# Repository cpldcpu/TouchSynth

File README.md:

# TouchSynth

**[Blog article](https://cpldcpu.github.io/2026/11/14/touchsynth/)** · **[Audio samples](https://cpldcpu.github.io/TouchSynth/)**

---

A small MCU-controlled analog monophonic synthesizer on a 100 × 100 mm, 4-layer PCB. It has no
potentiometers and no mechanical switches: 13 capacitive touch keys plus SHIFT / − / + play and edit it, and
16 LEDs show the settings. A CH32V003 (or CH32V002 / V006) generates the oscillator timing and four
PWM control voltages for a discrete analog voice:

- **DCO:** a TL072 integrator reset by the MCU timer. The charge current tracks pitch, so the saw amplitude
  stays flat. Saw, variable-width pulse, sub-oscillator and noise.
- **VCF:** a 24 dB/oct transistor ladder (BC847BS) with an expo converter and resonance up to self-oscillation.
- **VCA:** a differential-pair VCA. An 8-bit R-2R trim DAC nulls the CV feedthrough ("thump").
- **Line out,** an audio loopback into the MCU ADC (for calibration and tests), and an optional MIDI in.

All assembled parts are JLCPCB **Basic** or **Promotional Extended** parts: 40 BOM lines, 196 placements,
about USD 3.65 of parts per board at list price. The MCU, headers and MIDI parts are hand-soldered.

**Status (2026-10-18):** board 1 (rev 0.1, CH32V006) is built and brought up. It passes the bring-up steps
and functional tests T1, T2 and T4–T12 (noise marginal at about −55 dB); T3 (touch scan rate) and T14 (MIDI)
have not been measured. The results are in the
[design report](docs/report/touchsynth_report.pdf), section 10. Firmware 0.1 runs on the board, including
multitrack demo pieces and percussion presets. Calibration storage in flash is still open.

The `polyphonic_exp` branch experiments with extensions. So far it turns the pulse output into a PWM DAC
(CH32V006) for digital voices through the analog filter and VCA, starting with a modal timpani, the *kettle*
([kettle_model.mp3](docs/audio/pieces/kettle_model.mp3); report, section 10.5).

Design: cpldcpu & Claude Opus 5.5.

## Hear it

Recorded from board 1's line out. The synth is monophonic, so the multitrack pieces were played one part at a
time and mixed:

| Piece | Board 1 | Model |
|---|---|---|
| *TouchSynth Demo*, original, 7 parts (drums, acid bass, arp, lead, pad) | [demo_hw](docs/audio/demo/touchsynth_demo_hw.mp3) | [demo_model](docs/audio/demo/touchsynth_demo_model.mp3) |
| Purcell, *Queen Mary's March*: 4 trumpets, bass, timpani (modal synthesis on the PWM DAC) | [march_hw](docs/audio/pieces/march_hw.mp3) | [march_model](docs/audio/pieces/march_model.mp3) |
| Bach, Toccata BWV 565, mm. 1–30: 9 organ voices | [toccata_hw](docs/audio/pieces/toccata_hw.mp3) | [toccata_model](docs/audio/pieces/toccata_model.mp3) |
| *Aerosphere*, original space-synth piece, 8 parts | [aero_hw](docs/audio/pieces/aero_hw.mp3) | [aero_model](docs/audio/pieces/aero_model.mp3) |
| Suite: Aerosphere intro into the Toccata | [suite_hw](docs/audio/pieces/suite_hw.mp3) | [suite_model](docs/audio/pieces/suite_model.mp3) |

The three built-in demo tunes (SHIFT + C' on the board), recorded from board 1:
[acid](docs/audio/hw_board1/tune_acid.mp3), [prelude](docs/audio/hw_board1/tune_prelude.mp3) (Bach BWV 846) and
[ode](docs/audio/hw_board1/tune_ode.mp3) (Beethoven). Also from the board: a
[waveform tour](docs/audio/hw_board1/waveforms.mp3) and a [scale on the self-oscillating filter](docs/audio/hw_board1/selfosc_scale.mp3).
The behavioural model renders every single feature (waveforms, filter, envelopes, glide, …) in
[docs/audio/features/](docs/audio/features/). [docs/README.md](docs/README.md) lists all audio files.

## Documents

| Document | Content |
|---|---|
| [docs/report/touchsynth_report.pdf](docs/report/touchsynth_report.pdf) | **design report**: requirements, architecture, circuits, simulations, PCB, BOM, firmware, demo tunes and instruments, V&V with the board 1 results |
| [docs/README.md](docs/README.md) | index of everything in `docs/`: documents, figures, result data, audio |
| [docs/spec.md](docs/spec.md) | specification and design decisions (some pre-layout details are outdated; the report is current) |
| [docs/sim_report.md](docs/sim_report.md) | simulation report S1–S7 and the behavioural model |
| [docs/verification_plan.md](docs/verification_plan.md) | bring-up, functional tests, calibration and validation, board 1 results |
| [docs/touchsynth_schematic.pdf](docs/touchsynth_schematic.pdf) | schematic (7 sheets) |
| [firmware/touchsynth/README.md](firmware/touchsynth/README.md) | firmware build, playing instructions and test console |
| [hw/README.md](hw/README.md) | schematic generator scripts |

## Repository layout

```
docs/        report (LaTeX), spec, simulation report, V&V plan, figures, audio examples, result CSVs
sim/         ngspice simulations S1–S7 (one folder per block), shared netlists and models, behavioural model
hw/          design.py (single source of truth) -> KiCad schematic, PCB, routing and fab outputs
  touchsynth/  KiCad 10 project (generated; edit the Python sources, not the KiCad files)
firmware/    touchsynth/ firmware 0.1, ch32fun (git submodule)
parts/       JLCPCB Basic / Promotional Extended part lists
tools/       bench tools: hardware tests, scope recording, multitrack mixing, figures; Freerouting jar (not in git)
```

## Flow

Every stage is generated by scripts from [hw/design.py](hw/design.py), which holds the parts, values, LCSC
numbers and nets.

```
simulate      sim/s*/s*.py                 ngspice-42 in WSL -> docs/results/*.csv, docs/figures/*.png
model         sim/behav/validate.py        behavioural model vs. ngspice
              sim/behav/examples.py        audio examples + spectrograms
schematic     hw/gen_sch2.py               -> hw/touchsynth/*.kicad_sch
              hw/check_netlist.py          KiCad netlist == design.py
              hw/check_sim.py              design.py == simulation netlists
PCB           hw/gen_pcb.py [--route]      placement, silkscreen art, planes, Freerouting + GND stitching
              hw/gen_pcb.py --finish       post-route clean-up (islands, leftovers via the A* router)
fab           hw/fab.py                    gerbers, drill, BOM and CPL -> hw/touchsynth/production/
report        docs/report/gen_tables.py    then: latexmk -pdf touchsynth_report.tex (WSL)
firmware      firmware/touchsynth/gen_tables.py, check_pins.py, make
tunes         sim/behav/tunes.py, pieces.py    demo tunes, multitrack pieces and presets (-> firmware tables)
bench         tools/hwtest.py              functional tests over the SWIO console -> docs/results/hw_board1*
              tools/hw_figures.py          board 1 figures for the report
              tools/record_parts.sh        record one multitrack part per take with the scope (on the lab PC)
              tools/mix_parts.py, suite.py align, clock-correct and mix the takes -> docs/audio/
```

The bench tools need the lab setup (the PC with the programmer, the scope address) in `tools/lab.conf`: copy
[tools/lab.conf.example](tools/lab.conf.example) and edit it; `lab.conf` is not in git.

`gen_pcb.py` needs KiCad's bundled Python (`pcbnew`) and Java 17 for Freerouting 1.9.0. The hw scripts find KiCad 10
in its standard install folder, or in `KICAD_DIR` if set. The other Python
scripts use a normal Python 3 with numpy and matplotlib. ngspice, LaTeX and the RISC-V toolchain run in WSL.

## Key numbers

| | |
|---|---|
| Supply | 9–12 V DC, about 31 mA (simulated); board 1: 25 mA, MCU running, LEDs off |
| Pitch range | C1 … C8, saw amplitude flat within ±2.2 % |
| Filter | 20 Hz … 20 kHz cutoff, −23 dB/oct, self-oscillation |
| VCA | 121 dB off-attenuation, thump < 0.6 mV after trim |
| Output | about 1.2 Vpp line level, AC-coupled |
| Control | 4 × 12-bit CV (10-bit PWM at 46.9 kHz + 2-bit dither), 1 kHz envelope / LFO rate |
| Touch | 16 pads via 2 × CD4051, 1.4 kHz scan |
| PCB | 100 × 100 mm, 4 layers (signal / GND / split power / signal), 242 parts, 166 nets |

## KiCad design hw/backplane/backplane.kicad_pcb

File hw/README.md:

# Hardware generator scripts (KiCad 10)

Everything here is generated from Python; edit the sources, not the `.kicad_sch` files. The scripts serve several
boards; `BOARD` selects one (`board.py`):

| `BOARD` | Design | Output | Status |
|---|---|---|---|
| `voice` (default) | `voice.py`: the voice card (docs/spec.md section 3) | `voice/` | schematic generated, hand-laid out (`layouts_voice.py`) and checked; PCB generated and routed (`voice/voice.kicad_pcb`, 50 × 50 mm, 4 layers, DRC clean, stereo pan stage S13 A) |
| `backplane` | `backplane.py`: the backplane and controller (docs/backplane.md) | `backplane/` | schematic hand-laid out (`layouts_backplane.py`) and checked (mixer against S12 `--bus2`); PCB generated and routed (`gen_pcb_bp.py`, 100 × 100 mm, 4 layers: In1 GND, In2 +3V3 / GND; DRC clean); host port fitted, slot 1 convertible to an effects slot (backplane.md 5.1) |
| `touchsynth` | `design.py`: TouchSynth rev 0.1, for reference | `touchsynth/` (its KiCad project is on `master`) | |

| File | Role |
|---|---|
| `voice.py`, `design.py` | single source of truth per board: parts (value, footprint, LCSC, sim name), nets, sheets, groups; `voice.py` also maps its simulation netlist (S13 variant A on S10 v5c) to its nets |
| `board.py` | board selection (`BOARD`), project name, power nets, layout module |
| `lcsc.py` | picks JLCPCB basic / promotional parts for passives (voltage rating >= 2x working voltage; C0G on request) |
| `layouts_voice.py`, `layouts_backplane.py`, `layouts.py` | hand-drawn sheet layouts of the voice card, the backplane and rev 0.1; `layouts_none.py`: none (every part auto-placed, only the PWR_FLAGs drawn) |
| `draw.py` | drawing layer: geometric connectivity, auto-labels for split nets, short detection, junctions |
| `gen_sch2.py` | writes the schematic (`<board>/*.kicad_sch`) — **use this one** |
| `gen_sch.py` | v1 generator (label-only layout); its writer functions are reused by v2 |
| `check_netlist.py` | exports the KiCad netlist and compares it with the design |
| `check_sim.py` | compares the design with its ngspice netlist (nodes and values of every simulated element) |
| `gen_pcb.py` | voice card PCB (KiCad's Python): places from `pcb_place.py`, adds zones and silkscreen; `--route` adds plane vias, routes with Freerouting (`FREEROUTING_JAR`, else `tools/` or `archive/tools/freerouting-1.9.0.jar`), stitches, rips up and repairs open nets (20–30 min per pass; Freerouting's results vary between runs); `--repair`, `--finish`, `--polish` (re-route the listed analog nets), `--art` (front silk on a routed board), `--corridor` |
| `pcb_place.py` | floorplan: anchors, blocks, In2 plane polygons, edge routes (SWIO), pre-routes, polish list |
| `gen_pcb_bp.py`, `pcb_place_bp.py`, `pcb_art_bp.py` | backplane PCB (4 layers; `BP_LAYERS=2` routes the same placement on 2 as a check): generator with the locked pre-routes (+5 V trunk and rail, bus in the socket field, audio fan-out, summing band on B.Cu), GND as its own net class skipped by Freerouting; floorplan; silkscreen art (`--art` redoes it and the DNP / BOM flags on a routed board) |
| `pcb_figures.py` | layer plots and 3D renders of a board into `docs/figures/<board>_pcb/` |
| `pcb_art.py` | silkscreen, front and back |
| `pcb_gnd.py`, `pcb_maze.py` | GND island bridging, grid maze router for leftover connections |
| `fab.py` | JLCPCB gerbers, drill, BOM, CPL into `<board>/production/` (gitignored) |
| `lib/TouchSynth.pretty` | rev 0.1 touch-key footprints |

```
python gen_sch2.py && kicad-cli sch erc voice/voice.kicad_sch && python check_netlist.py && python check_sim.py
<KiCad 10>/bin/python.exe gen_pcb.py --route && kicad-cli pcb drc --schematic-parity voice/voice.kicad_pcb && python fab.py
```

The backplane (about an hour of routing; `BP_LAYERS=2` routes the same placement on two layers into
`backplane/backplane_2l.kicad_pcb`, as a check):

```
export BOARD=backplane
python gen_sch2.py && kicad-cli sch erc backplane/backplane.kicad_sch && python check_netlist.py && python check_sim.py
<KiCad 10>/bin/python.exe gen_pcb_bp.py --route && <KiCad 10>/bin/python.exe gen_pcb_bp.py --art
kicad-cli pcb drc --schematic-parity backplane/backplane.kicad_pcb && python pcb_figures.py && python fab.py
```

PCB figures for the docs (layer plots, 3D renders into `docs/figures/<board>_pcb/`): `python pcb_figures.py`.

After a schematic change, export the PDF for the docs (from the repository root):
`kicad-cli sch export pdf -o docs/schematics/<board>.pdf hw/<board>/<board>.kicad_sch`.

The rev 0.1 PCB scripts are on `master`.

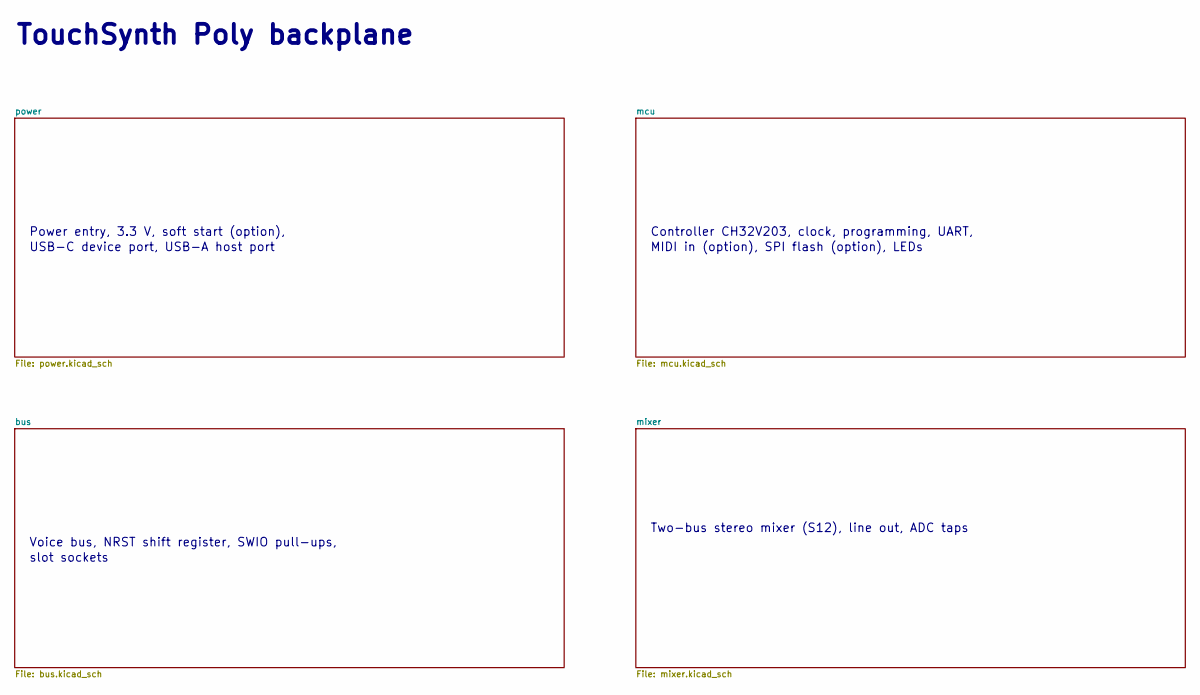
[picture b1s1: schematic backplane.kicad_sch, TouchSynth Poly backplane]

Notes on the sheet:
Power entry, 3.3 V, soft start (option),
USB-C device port, USB-A host port
Controller CH32V203, clock, programming, UART,
MIDI in (option), SPI flash (option), LEDs
Voice bus, NRST shift register, SWIO pull-ups,
slot sockets
Two-bus stereo mixer (S12), line out, ADC taps
TouchSynth Poly backplane

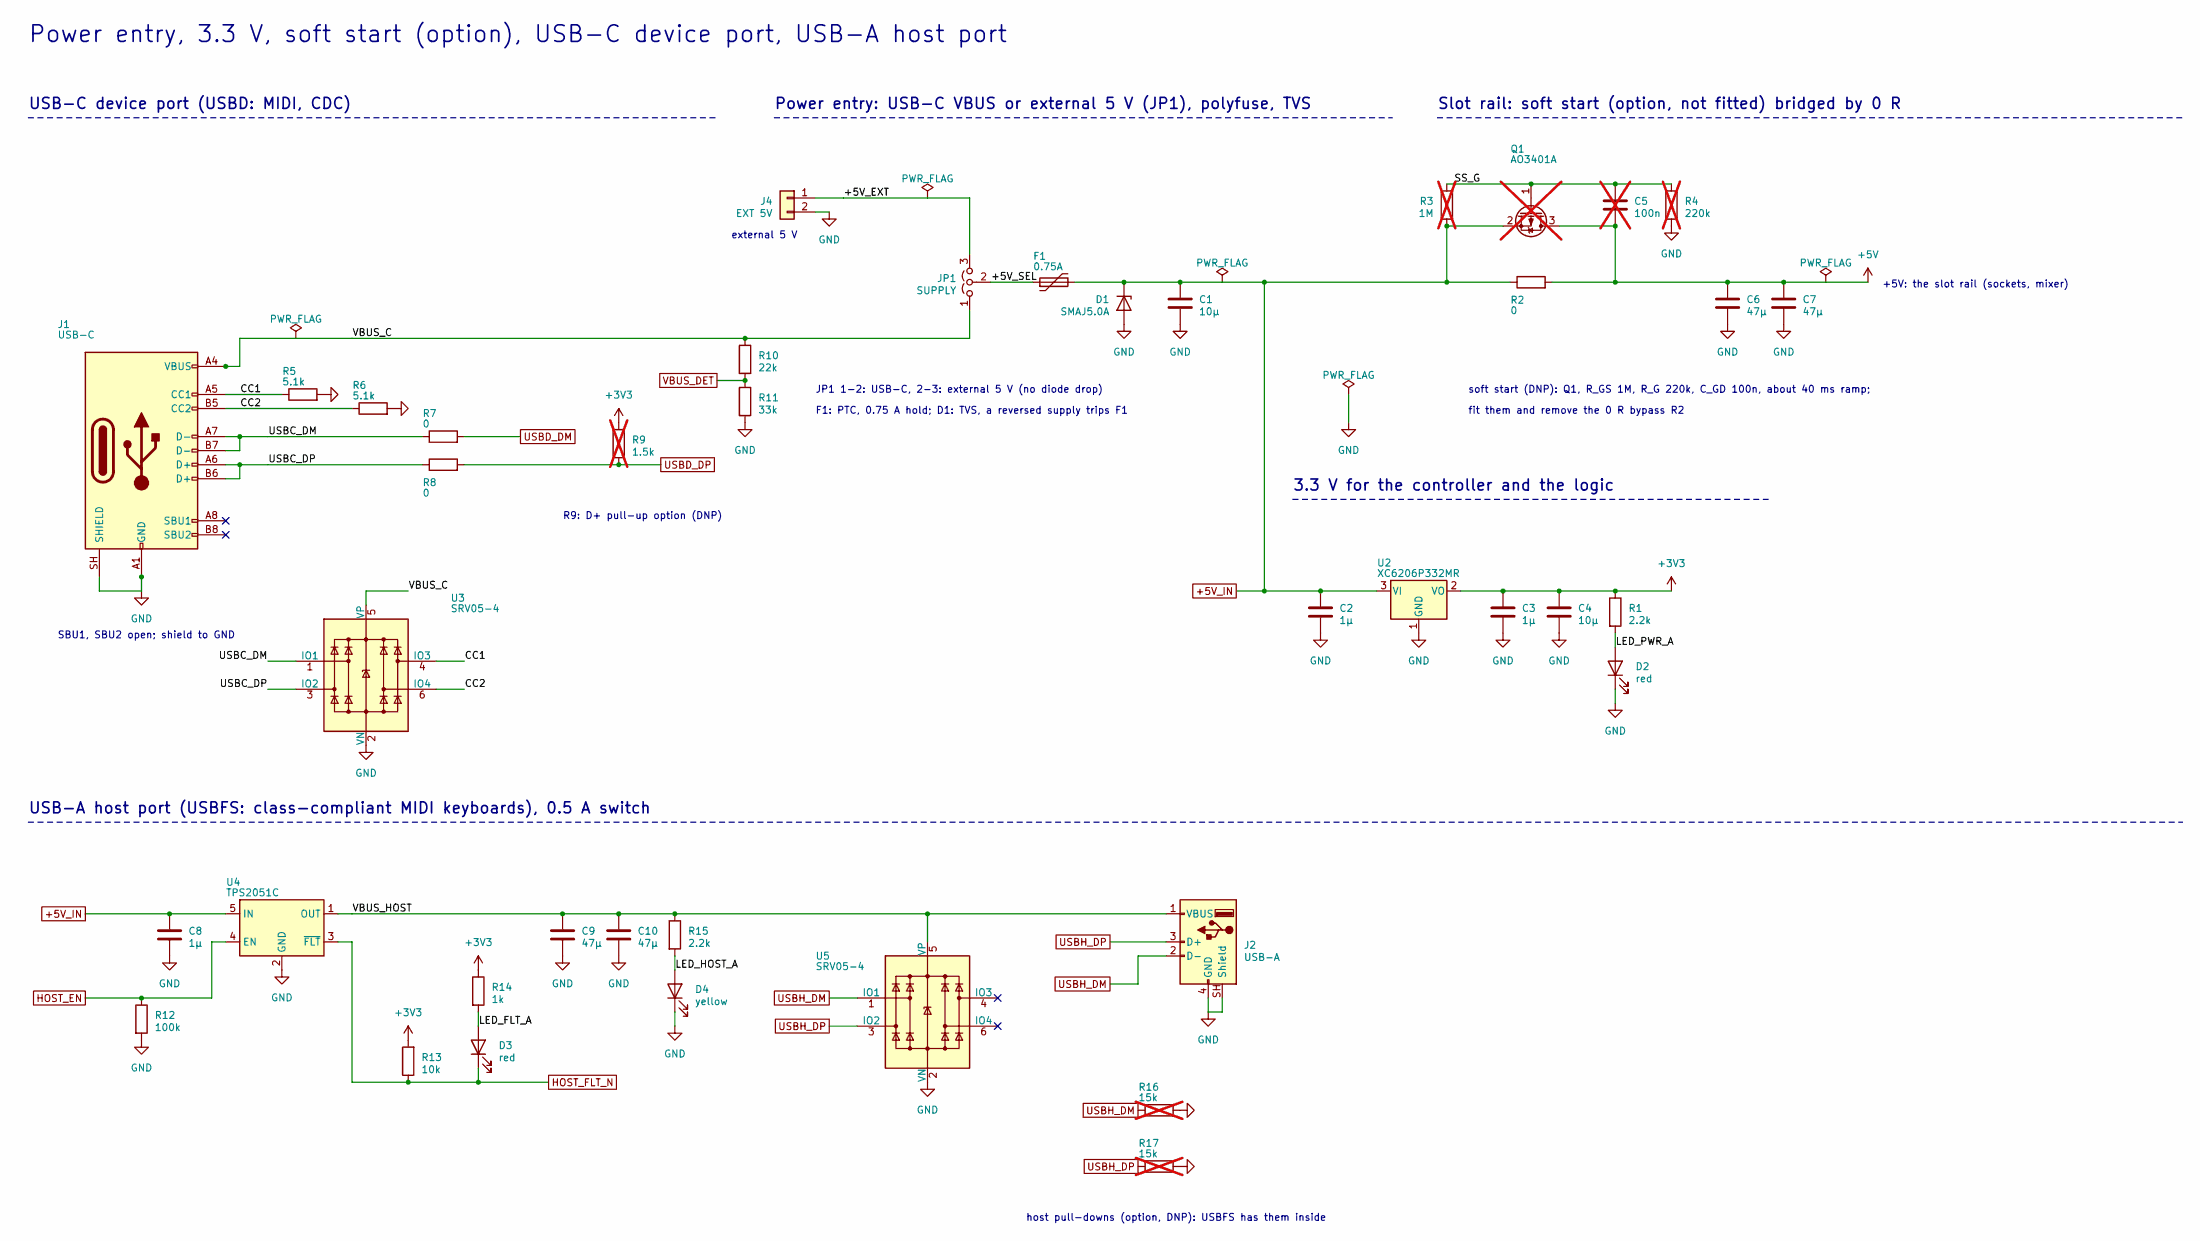
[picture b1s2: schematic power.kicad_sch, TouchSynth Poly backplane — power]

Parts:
C1, C4: 10µ; C_0603_1608Metric; LCSC C19702
C2, C3, C8: 1µ; C_0603_1608Metric; LCSC C15849
C5: 100n; C_0603_1608Metric; LCSC C14663; not fitted
C6, C7, C9, C10: 47µ; C_1206_3216Metric; LCSC C96123
D1: SMAJ5.0A; D_SMA; LCSC C2925443
D2, D3: red; LED_0603_1608Metric; LCSC C2286
D4: yellow; LED_0603_1608Metric; LCSC C89811
F1: 0.75A; Fuse_1206_3216Metric
J1: USB-C; USB_C_Receptacle_GCT_USB4105-xx-A_16P_TopMnt_Horizontal
J2: USB-A; USB_A_Molex_67643_Horizontal
J4: EXT 5V; PinHeader_1x02_P2.54mm_Vertical
JP1: SUPPLY; PinHeader_1x03_P2.54mm_Vertical
Q1: AO3401A; SOT-23; LCSC C15127; not fitted
R1, R15: 2.2k; R_0603_1608Metric; LCSC C4190
R2: 0; R_1206_3216Metric; LCSC C17888
R3: 1M; R_0603_1608Metric; LCSC C22935; not fitted
R4: 220k; R_0603_1608Metric; LCSC C22961; not fitted
R5, R6: 5.1k; R_0603_1608Metric; LCSC C23186
R7, R8: 0; R_0603_1608Metric; LCSC C21189
R9: 1.5k; R_0603_1608Metric; LCSC C22843; not fitted
R10: 22k; R_0603_1608Metric; LCSC C31850
R11: 33k; R_0603_1608Metric; LCSC C4216
R12: 100k; R_0603_1608Metric; LCSC C25803
R13: 10k; R_0603_1608Metric; LCSC C25804
R14: 1k; R_0603_1608Metric; LCSC C21190
R16, R17: 15k; R_0603_1608Metric; LCSC C22809; not fitted
U2: XC6206P332MR; SOT-23; LCSC C5446
U3, U5: SRV05-4; SOT-23-6; LCSC C7420376
U4: TPS2051C; SOT-23-5

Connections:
+3V3: C3.1, C4.1, R1.1, R9.2, R13.2, R14.1, U2.2 (VO); also elsewhere on the board
+5V: C5.2, C6.1, C7.1, Q1.3 (D), R2.2; also elsewhere on the board
+5V_IN: C1.1, C2.1, C8.1, D1.1 (K), F1.2, Q1.2 (S), R2.1, R3.1, U2.3 (VI), U4.5 (IN)
/power/+5V_EXT: J4.1, JP1.3 (B)
/power/+5V_SEL: F1.1, JP1.2 (C)
/power/CC1: J1.A5 (CC1), R5.1, U3.4 (IO3)
/power/CC2: J1.B5 (CC2), R6.1, U3.6 (IO4)
/power/LED_FLT_A: D3.2 (A), R14.2
/power/LED_HOST_A: D4.2 (A), R15.2
/power/LED_PWR_A: D2.2 (A), R1.2
/power/SS_G: C5.1, Q1.1 (G), R3.2, R4.1
/power/USBC_DM: J1.A7 (D-), J1.B7 (D-), R7.1, U3.1 (IO1)
/power/USBC_DP: J1.A6 (D+), J1.B6 (D+), R8.1, U3.3 (IO2)
/power/VBUS_C: J1.A4 (VBUS), J1.A9 (VBUS), J1.B4 (VBUS), J1.B9 (VBUS), JP1.1 (A), R10.1, U3.5 (VP)
/power/VBUS_HOST: C9.1, C10.1, J2.1 (VBUS), R15.1, U4.1 (OUT), U5.5 (VP)
GND: C1.2, C2.2, C3.2, C4.2, C6.2, C7.2, C8.2, C9.2, C10.2, D1.2 (A), D2.1 (K), D4.1 (K), J1.A1 (GND), J1.A12 (GND), J1.B1 (GND), J1.B12 (GND), J1.SH (SHIELD), J2.4 (GND), J2.SH (Shield), J4.2, R4.2, R5.2, R6.2, R11.2, R12.2, R16.2, R17.2, U2.1 (GND), U3.2 (VN), U4.2 (GND), U5.2 (VN); also elsewhere on the board
HOST_EN: R12.1, U4.4 (EN); also elsewhere on the board
HOST_FLT_N: D3.1 (K), R13.1, U4.3 (~FLT); also elsewhere on the board
USBD_DM: R7.2; also elsewhere on the board
USBD_DP: R8.2, R9.1; also elsewhere on the board
USBH_DM: J2.2 (D-), R16.1, U5.1 (IO1); also elsewhere on the board
USBH_DP: J2.3 (D+), R17.1, U5.3 (IO2); also elsewhere on the board
VBUS_DET: R10.2, R11.1; also elsewhere on the board

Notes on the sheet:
Power entry, 3.3 V, soft start (option), USB-C device port, USB-A host port
USB-C device port (USBD: MIDI, CDC)
R9: D+ pull-up option (DNP)
SBU1, SBU2 open; shield to GND
Power entry: USB-C VBUS or external 5 V (JP1), polyfuse, TVS
external 5 V
JP1 1-2: USB-C, 2-3: external 5 V (no diode drop)
F1: PTC, 0.75 A hold; D1: TVS, a reversed supply trips F1
3.3 V for the controller and the logic
Slot rail: soft start (option, not fitted) bridged by 0 R
+5V: the slot rail (sockets, mixer)
soft start (DNP): Q1, R_GS 1M, R_G 220k, C_GD 100n, about 40 ms ramp;
fit them and remove the 0 R bypass R2
USB-A host port (USBFS: class-compliant MIDI keyboards), 0.5 A switch
host pull-downs (option, DNP): USBFS has them inside

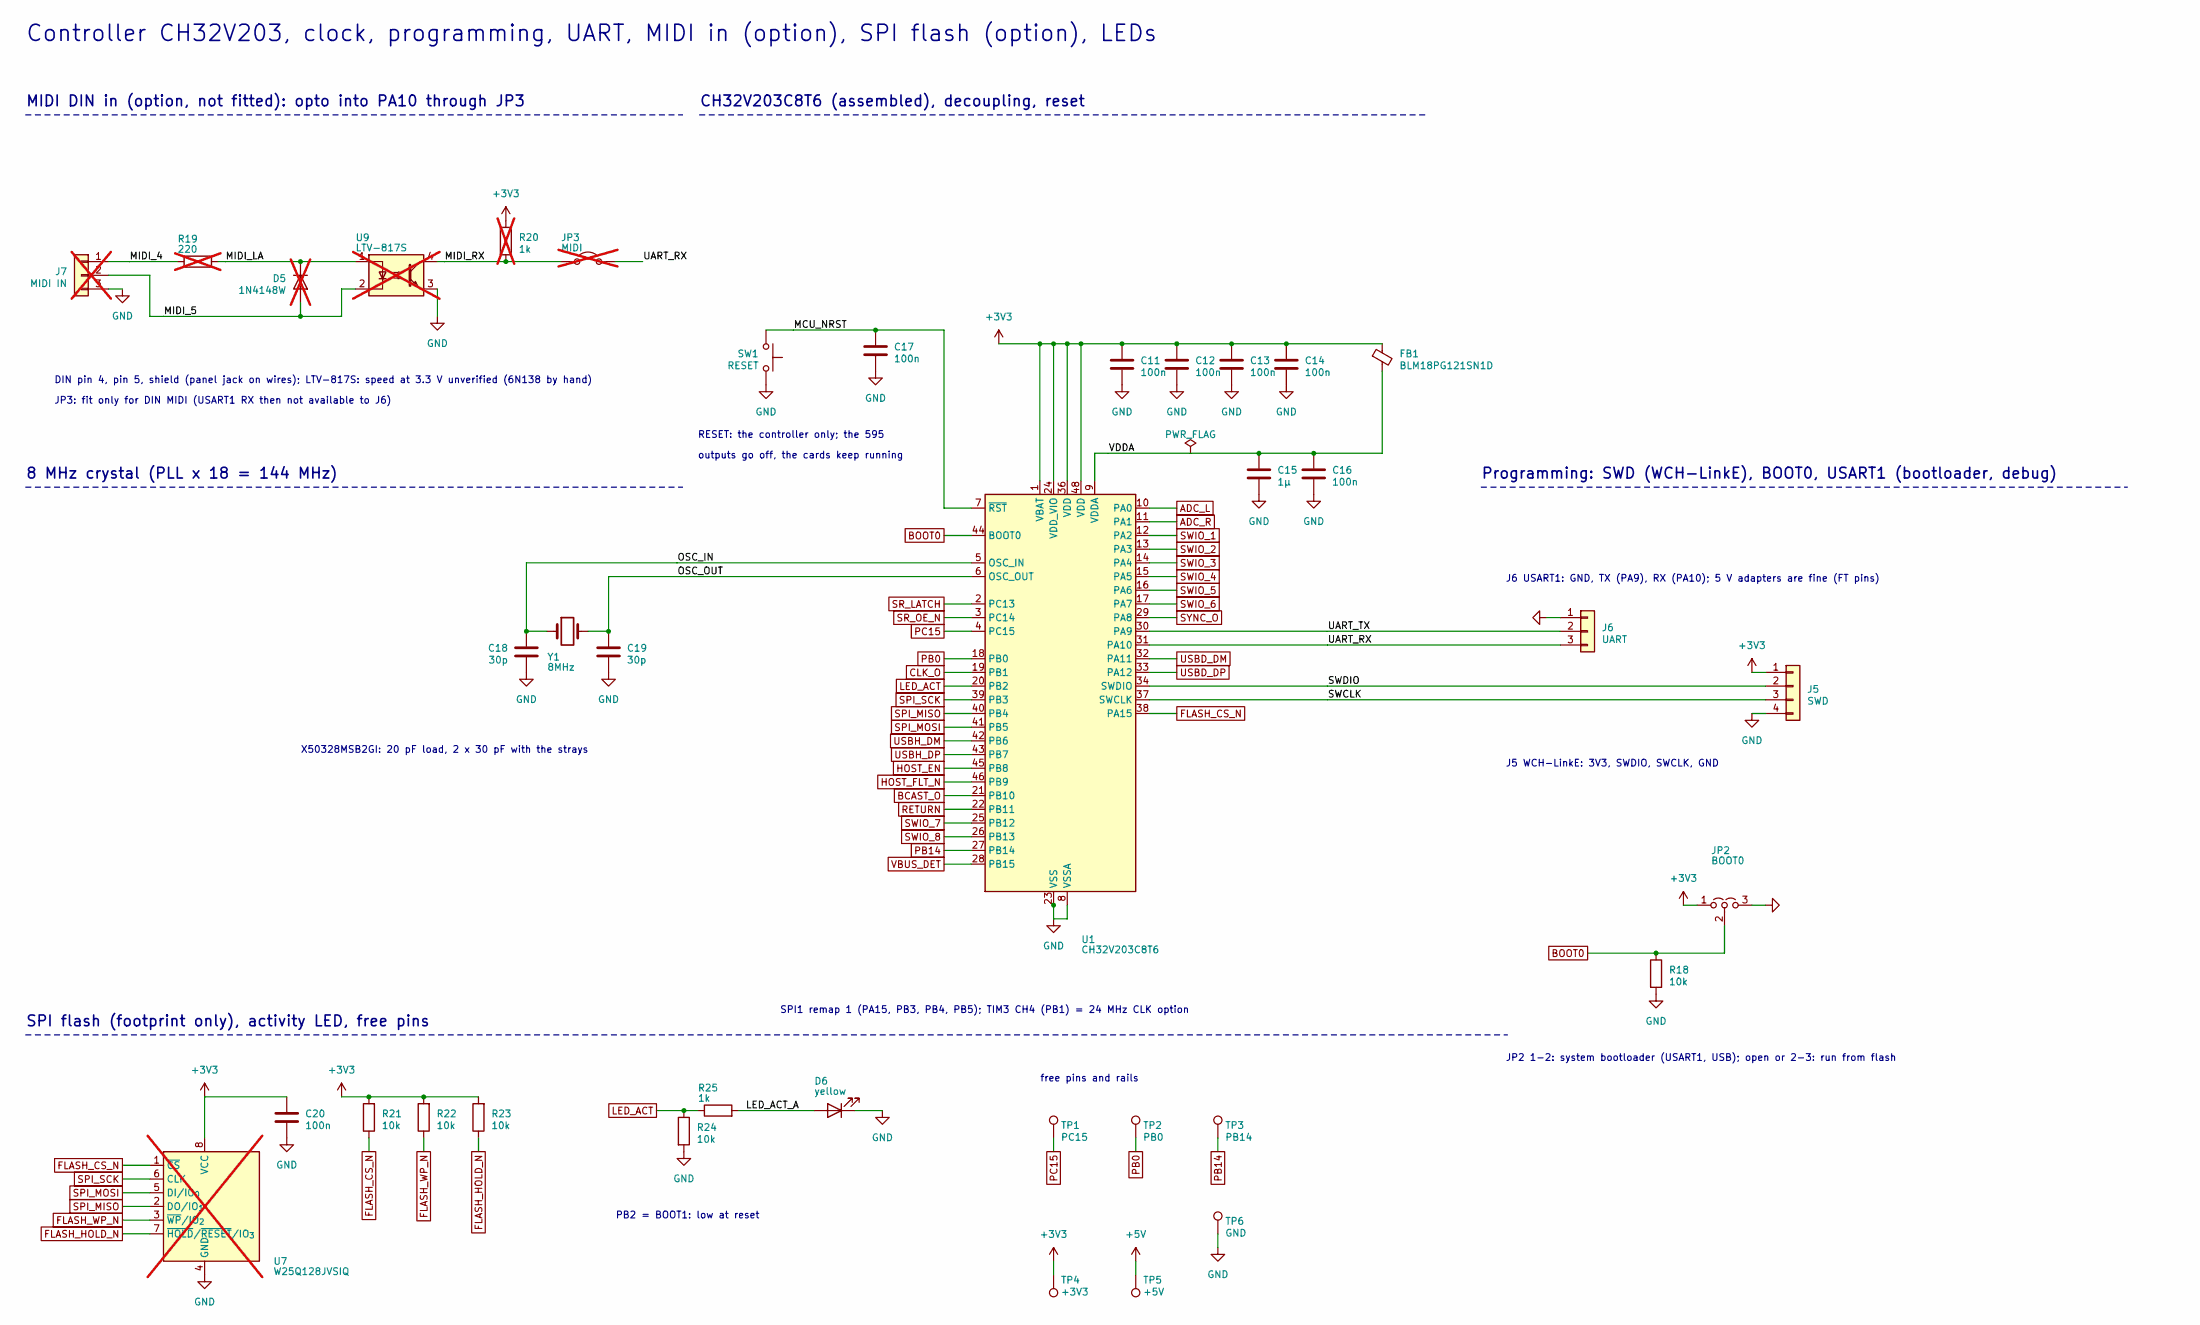
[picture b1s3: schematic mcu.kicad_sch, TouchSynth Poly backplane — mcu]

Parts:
C11, C12, C13, C14, C16, C17, C20: 100n; C_0603_1608Metric; LCSC C14663
C15: 1µ; C_0603_1608Metric; LCSC C15849
C18, C19: 30p; C_0603_1608Metric; LCSC C1658
D5: 1N4148W; D_SOD-123; LCSC C81598; not fitted
D6: yellow; LED_0603_1608Metric; LCSC C89811
FB1: BLM18PG121SN1D; L_0603_1608Metric; LCSC C14709
J5: SWD; PinHeader_1x04_P2.54mm_Vertical
J6: UART; PinHeader_1x03_P2.54mm_Vertical
J7: MIDI IN; PinHeader_1x03_P2.54mm_Vertical; not fitted
JP2: BOOT0; PinHeader_1x03_P2.54mm_Vertical
JP3: MIDI; PinHeader_1x02_P2.54mm_Vertical; not fitted
R18, R21, R22, R23, R24: 10k; R_0603_1608Metric; LCSC C25804
R19: 220; R_0603_1608Metric; LCSC C22962; not fitted
R20: 1k; R_0603_1608Metric; LCSC C21190; not fitted
R25: 1k; R_0603_1608Metric; LCSC C21190
SW1: RESET; SW_Push_1P1T_XKB_TS-1187A; LCSC C318884
TP1: PC15; TestPoint_Pad_D1.0mm
TP2: PB0; TestPoint_Pad_D1.0mm
TP3: PB14; TestPoint_Pad_D1.0mm
TP4: +3V3; TestPoint_Pad_D1.0mm
TP5: +5V; TestPoint_Pad_D1.0mm
TP6: GND; TestPoint_Pad_D1.0mm
U1: CH32V203C8T6; LQFP-48_7x7mm_P0.5mm; LCSC C3001172
U7: W25Q128JVSIQ; SOIC-8_5.3x5.3mm_P1.27mm; LCSC C97521; not fitted
U9: LTV-817S; SMDIP-4_W9.53mm; LCSC C109227; not fitted
Y1: 8MHz; Crystal_SMD_5032-2Pin_5.0x3.2mm; LCSC C115962

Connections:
+3V3: C11.1, C12.1, C13.1, C14.1, C20.1, FB1.1, J5.1, JP2.1 (A), R20.2, R21.2, R22.2, R23.2, TP4.1, U1.1 (VBAT), U1.24 (VDD_VIO), U1.36 (VDD), U1.48 (VDD), U7.8 (VCC); also elsewhere on the board
+5V: TP5.1; also elsewhere on the board
/mcu/LED_ACT_A: D6.2 (A), R25.2
/mcu/MCU_NRST: C17.1, SW1.1, U1.7 (~RST)
/mcu/MIDI_4: J7.1, R19.1
/mcu/MIDI_5: D5.2 (A), J7.2, U9.2
/mcu/MIDI_LA: D5.1 (K), R19.2, U9.1
/mcu/MIDI_RX: JP3.1 (A), R20.1, U9.4
/mcu/OSC_IN: C18.1, U1.5 (OSC_IN), Y1.1
/mcu/OSC_OUT: C19.1, U1.6 (OSC_OUT), Y1.2
/mcu/SWCLK: J5.3, U1.37 (SWCLK)
/mcu/SWDIO: J5.2, U1.34 (SWDIO)
/mcu/UART_RX: J6.3, JP3.2 (B), U1.31 (PA10)
/mcu/UART_TX: J6.2, U1.30 (PA9)
/mcu/VDDA: C15.1, C16.1, FB1.2, U1.9 (VDDA)
ADC_L: U1.10 (PA0); also elsewhere on the board
ADC_R: U1.11 (PA1); also elsewhere on the board
BCAST_O: U1.21 (PB10); also elsewhere on the board
BOOT0: JP2.2 (C), R18.1, U1.44 (BOOT0)
CLK_O: U1.19 (PB1); also elsewhere on the board
FLASH_CS_N: R21.1, U1.38 (PA15), U7.1 (~CS)
FLASH_HOLD_N: R23.1, U7.7 (~HOLD/~RESET/IO_{3})
FLASH_WP_N: R22.1, U7.3 (~WP/IO_{2})
GND: C11.2, C12.2, C13.2, C14.2, C15.2, C16.2, C17.2, C18.2, C19.2, C20.2, D6.1 (K), J5.4, J6.1, J7.3, JP2.3 (B), R18.2, R24.2, SW1.2, TP6.1, U1.8 (VSSA), U1.23 (VSS), U1.35 (VSS), U1.47 (VSS), U7.4 (GND), U9.3; also elsewhere on the board
HOST_EN: U1.45 (PB8); also elsewhere on the board
HOST_FLT_N: U1.46 (PB9); also elsewhere on the board
LED_ACT: R24.1, R25.1, U1.20 (PB2)
PB0: TP2.1, U1.18 (PB0)
PB14: TP3.1, U1.27 (PB14)
PC15: TP1.1, U1.4 (PC15)
RETURN: U1.22 (PB11); also elsewhere on the board
SPI_MISO: U1.40 (PB4), U7.2 (DO/IO_{1})
SPI_MOSI: U1.41 (PB5), U7.5 (DI/IO_{0}); also elsewhere on the board
SPI_SCK: U1.39 (PB3), U7.6 (CLK); also elsewhere on the board
SR_LATCH: U1.2 (PC13); also elsewhere on the board
SR_OE_N: U1.3 (PC14); also elsewhere on the board
SWIO_1: U1.12 (PA2); also elsewhere on the board
SWIO_2: U1.13 (PA3); also elsewhere on the board
SWIO_3: U1.14 (PA4); also elsewhere on the board
SWIO_4: U1.15 (PA5); also elsewhere on the board
SWIO_5: U1.16 (PA6); also elsewhere on the board
SWIO_6: U1.17 (PA7); also elsewhere on the board
SWIO_7: U1.25 (PB12); also elsewhere on the board
SWIO_8: U1.26 (PB13); also elsewhere on the board
SYNC_O: U1.29 (PA8); also elsewhere on the board
USBD_DM: U1.32 (PA11); also elsewhere on the board
USBD_DP: U1.33 (PA12); also elsewhere on the board
USBH_DM: U1.42 (PB6); also elsewhere on the board
USBH_DP: U1.43 (PB7); also elsewhere on the board
VBUS_DET: U1.28 (PB15); also elsewhere on the board

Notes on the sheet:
Controller CH32V203, clock, programming, UART, MIDI in (option), SPI flash (option), LEDs
CH32V203C8T6 (assembled), decoupling, reset
RESET: the controller only; the 595
outputs go off, the cards keep running
SPI1 remap 1 (PA15, PB3, PB4, PB5); TIM3 CH4 (PB1) = 24 MHz CLK option
8 MHz crystal (PLL x 18 = 144 MHz)
X50328MSB2GI: 20 pF load, 2 x 30 pF with the strays
MIDI DIN in (option, not fitted): opto into PA10 through JP3
DIN pin 4, pin 5, shield (panel jack on wires); LTV-817S: speed at 3.3 V unverified (6N138 by hand)
JP3: fit only for DIN MIDI (USART1 RX then not available to J6)
Programming: SWD (WCH-LinkE), BOOT0, USART1 (bootloader, debug)
J6 USART1: GND, TX (PA9), RX (PA10); 5 V adapters are fine (FT pins)
J5 WCH-LinkE: 3V3, SWDIO, SWCLK, GND
JP2 1-2: system bootloader (USART1, USB); open or 2-3: run from flash
SPI flash (footprint only), activity LED, free pins
PB2 = BOOT1: low at reset
free pins and rails

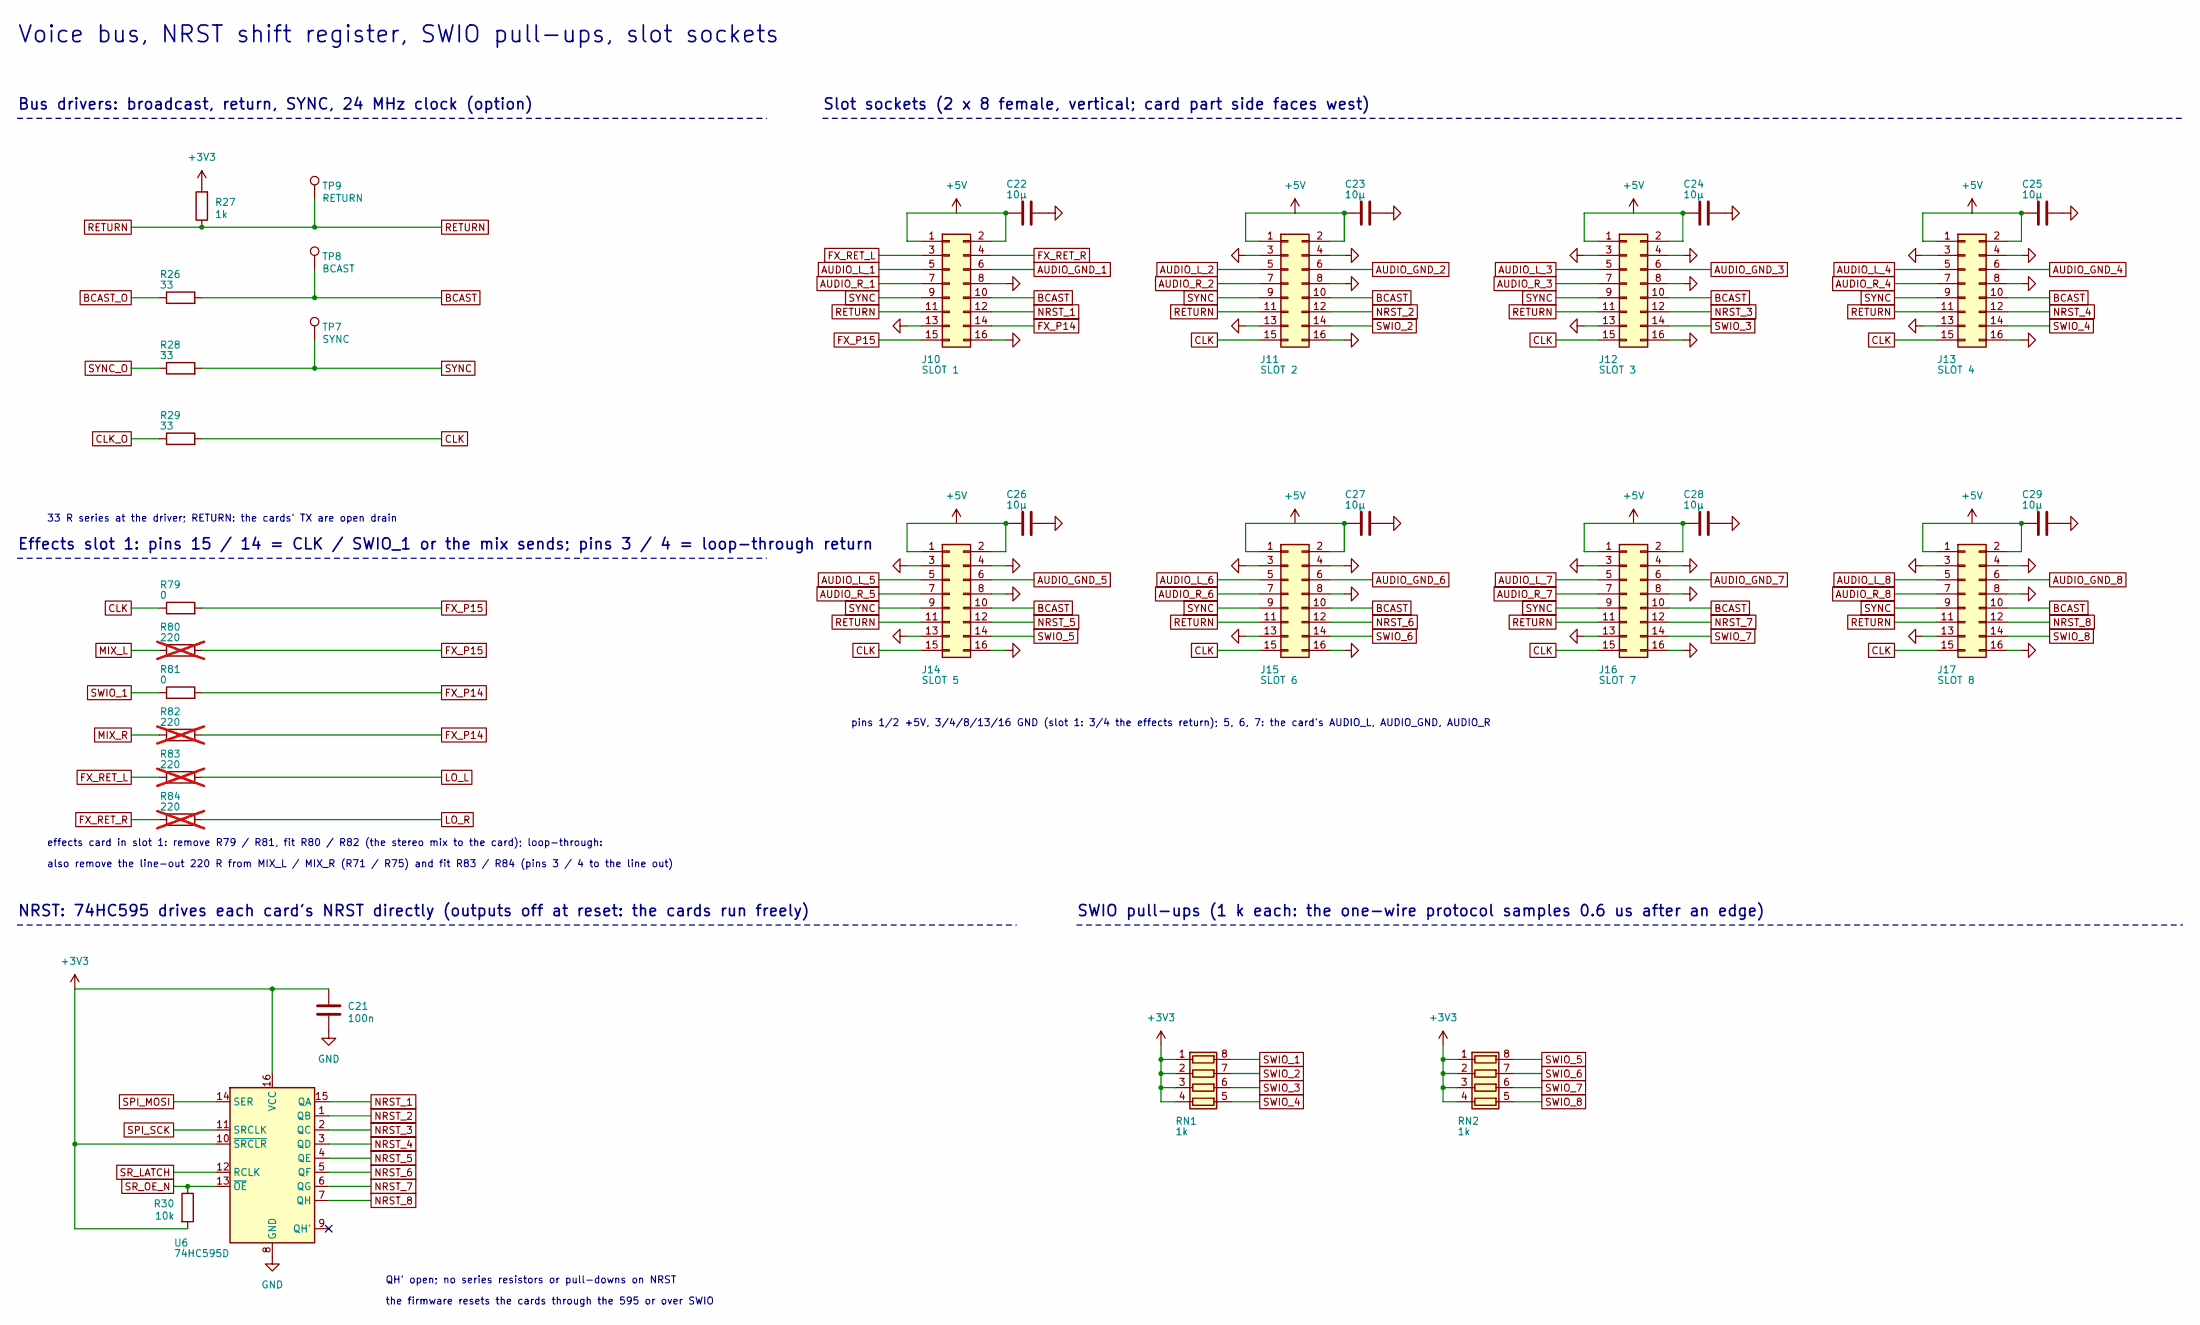
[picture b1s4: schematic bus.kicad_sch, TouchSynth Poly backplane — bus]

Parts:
C21: 100n; C_0603_1608Metric; LCSC C14663
C22, C23, C24, C25, C26, C27, C28, C29: 10µ; C_0603_1608Metric; LCSC C19702
J10: SLOT 1; PinSocket_2x08_P2.54mm_Vertical
J11: SLOT 2; PinSocket_2x08_P2.54mm_Vertical
J12: SLOT 3; PinSocket_2x08_P2.54mm_Vertical
J13: SLOT 4; PinSocket_2x08_P2.54mm_Vertical
J14: SLOT 5; PinSocket_2x08_P2.54mm_Vertical
J15: SLOT 6; PinSocket_2x08_P2.54mm_Vertical
J16: SLOT 7; PinSocket_2x08_P2.54mm_Vertical
J17: SLOT 8; PinSocket_2x08_P2.54mm_Vertical
R26, R28, R29: 33; R_0603_1608Metric; LCSC C23140
R27: 1k; R_0603_1608Metric; LCSC C21190
R30: 10k; R_0603_1608Metric; LCSC C25804
R79, R81: 0; R_0603_1608Metric; LCSC C21189
R80, R82, R83, R84: 220; R_0603_1608Metric; LCSC C22962; not fitted
RN1, RN2: 1k; R_Array_Convex_4x0603; LCSC C20197
TP7: SYNC; TestPoint_Pad_D1.0mm
TP8: BCAST; TestPoint_Pad_D1.0mm
TP9: RETURN; TestPoint_Pad_D1.0mm
U6: 74HC595D; SOIC-16_3.9x9.9mm_P1.27mm; LCSC C5947

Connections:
+3V3: C21.1, R27.2, R30.2, RN1.1 (R1.1), RN1.2 (R2.1), RN1.3 (R3.1), RN1.4 (R4.1), RN2.1 (R1.1), RN2.2 (R2.1), RN2.3 (R3.1), RN2.4 (R4.1), U6.10 (~SRCLR), U6.16 (VCC); also elsewhere on the board
+5V: C22.1, C23.1, C24.1, C25.1, C26.1, C27.1, C28.1, C29.1, J10.1, J10.2, J11.1, J11.2, J12.1, J12.2, J13.1, J13.2, J14.1, J14.2, J15.1, J15.2, J16.1, J16.2, J17.1, J17.2; also elsewhere on the board
AUDIO_GND_1: J10.6; also elsewhere on the board
AUDIO_GND_2: J11.6; also elsewhere on the board
AUDIO_GND_3: J12.6; also elsewhere on the board
AUDIO_GND_4: J13.6; also elsewhere on the board
AUDIO_GND_5: J14.6; also elsewhere on the board
AUDIO_GND_6: J15.6; also elsewhere on the board
AUDIO_GND_7: J16.6; also elsewhere on the board
AUDIO_GND_8: J17.6; also elsewhere on the board
AUDIO_L_1: J10.5; also elsewhere on the board
AUDIO_L_2: J11.5; also elsewhere on the board
AUDIO_L_3: J12.5; also elsewhere on the board
AUDIO_L_4: J13.5; also elsewhere on the board
AUDIO_L_5: J14.5; also elsewhere on the board
AUDIO_L_6: J15.5; also elsewhere on the board
AUDIO_L_7: J16.5; also elsewhere on the board
AUDIO_L_8: J17.5; also elsewhere on the board
AUDIO_R_1: J10.7; also elsewhere on the board
AUDIO_R_2: J11.7; also elsewhere on the board
AUDIO_R_3: J12.7; also elsewhere on the board
AUDIO_R_4: J13.7; also elsewhere on the board
AUDIO_R_5: J14.7; also elsewhere on the board
AUDIO_R_6: J15.7; also elsewhere on the board
AUDIO_R_7: J16.7; also elsewhere on the board
AUDIO_R_8: J17.7; also elsewhere on the board
BCAST: J10.10, J11.10, J12.10, J13.10, J14.10, J15.10, J16.10, J17.10, R26.2, TP8.1
BCAST_O: R26.1; also elsewhere on the board
CLK: J11.15, J12.15, J13.15, J14.15, J15.15, J16.15, J17.15, R29.2, R79.1
CLK_O: R29.1; also elsewhere on the board
FX_P14: J10.14, R81.2, R82.2
FX_P15: J10.15, R79.2, R80.2
FX_RET_L: J10.3, R83.1
FX_RET_R: J10.4, R84.1
GND: C21.2, C22.2, C23.2, C24.2, C25.2, C26.2, C27.2, C28.2, C29.2, J10.8, J10.13, J10.16, J11.3, J11.4, J11.8, J11.13, J11.16, J12.3, J12.4, J12.8, J12.13, J12.16, J13.3, J13.4, J13.8, J13.13, J13.16, J14.3, J14.4, J14.8, J14.13, J14.16, J15.3, J15.4, J15.8, J15.13, J15.16, J16.3, J16.4, J16.8, J16.13, J16.16, J17.3, J17.4, J17.8, J17.13, J17.16, U6.8 (GND); also elsewhere on the board
LO_L: R83.2; also elsewhere on the board
LO_R: R84.2; also elsewhere on the board
MIX_L: R80.1; also elsewhere on the board
MIX_R: R82.1; also elsewhere on the board
NRST_1: J10.12, U6.15 (QA)
NRST_2: J11.12, U6.1 (QB)
NRST_3: J12.12, U6.2 (QC)
NRST_4: J13.12, U6.3 (QD)
NRST_5: J14.12, U6.4 (QE)
NRST_6: J15.12, U6.5 (QF)
NRST_7: J16.12, U6.6 (QG)
NRST_8: J17.12, U6.7 (QH)
RETURN: J10.11, J11.11, J12.11, J13.11, J14.11, J15.11, J16.11, J17.11, R27.1, TP9.1; also elsewhere on the board
SPI_MOSI: U6.14 (SER); also elsewhere on the board
SPI_SCK: U6.11 (SRCLK); also elsewhere on the board
SR_LATCH: U6.12 (RCLK); also elsewhere on the board
SR_OE_N: R30.1, U6.13 (~OE); also elsewhere on the board
SWIO_1: R81.1, RN1.8 (R1.2); also elsewhere on the board
SWIO_2: J11.14, RN1.7 (R2.2); also elsewhere on the board
SWIO_3: J12.14, RN1.6 (R3.2); also elsewhere on the board
SWIO_4: J13.14, RN1.5 (R4.2); also elsewhere on the board
SWIO_5: J14.14, RN2.8 (R1.2); also elsewhere on the board
SWIO_6: J15.14, RN2.7 (R2.2); also elsewhere on the board
SWIO_7: J16.14, RN2.6 (R3.2); also elsewhere on the board
SWIO_8: J17.14, RN2.5 (R4.2); also elsewhere on the board
SYNC: J10.9, J11.9, J12.9, J13.9, J14.9, J15.9, J16.9, J17.9, R28.2, TP7.1
SYNC_O: R28.1; also elsewhere on the board

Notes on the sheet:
Voice bus, NRST shift register, SWIO pull-ups, slot sockets
Bus drivers: broadcast, return, SYNC, 24 MHz clock (option)
33 R series at the driver; RETURN: the cards' TX are open drain
Effects slot 1: pins 15 / 14 = CLK / SWIO_1 or the mix sends; pins 3 / 4 = loop-through return
effects card in slot 1: remove R79 / R81, fit R80 / R82 (the stereo mix to the card); loop-through:
also remove the line-out 220 R from MIX_L / MIX_R (R71 / R75) and fit R83 / R84 (pins 3 / 4 to the line out)
NRST: 74HC595 drives each card's NRST directly (outputs off at reset: the cards run freely)
QH' open; no series resistors or pull-downs on NRST
the firmware resets the cards through the 595 or over SWIO
SWIO pull-ups (1 k each: the one-wire protocol samples 0.6 us after an edge)
Slot sockets (2 x 8 female, vertical; card part side faces west)
pins 1/2 +5V, 3/4/8/13/16 GND (slot 1: 3/4 the effects return); 5, 6, 7: the card's AUDIO_L, AUDIO_GND, AUDIO_R
